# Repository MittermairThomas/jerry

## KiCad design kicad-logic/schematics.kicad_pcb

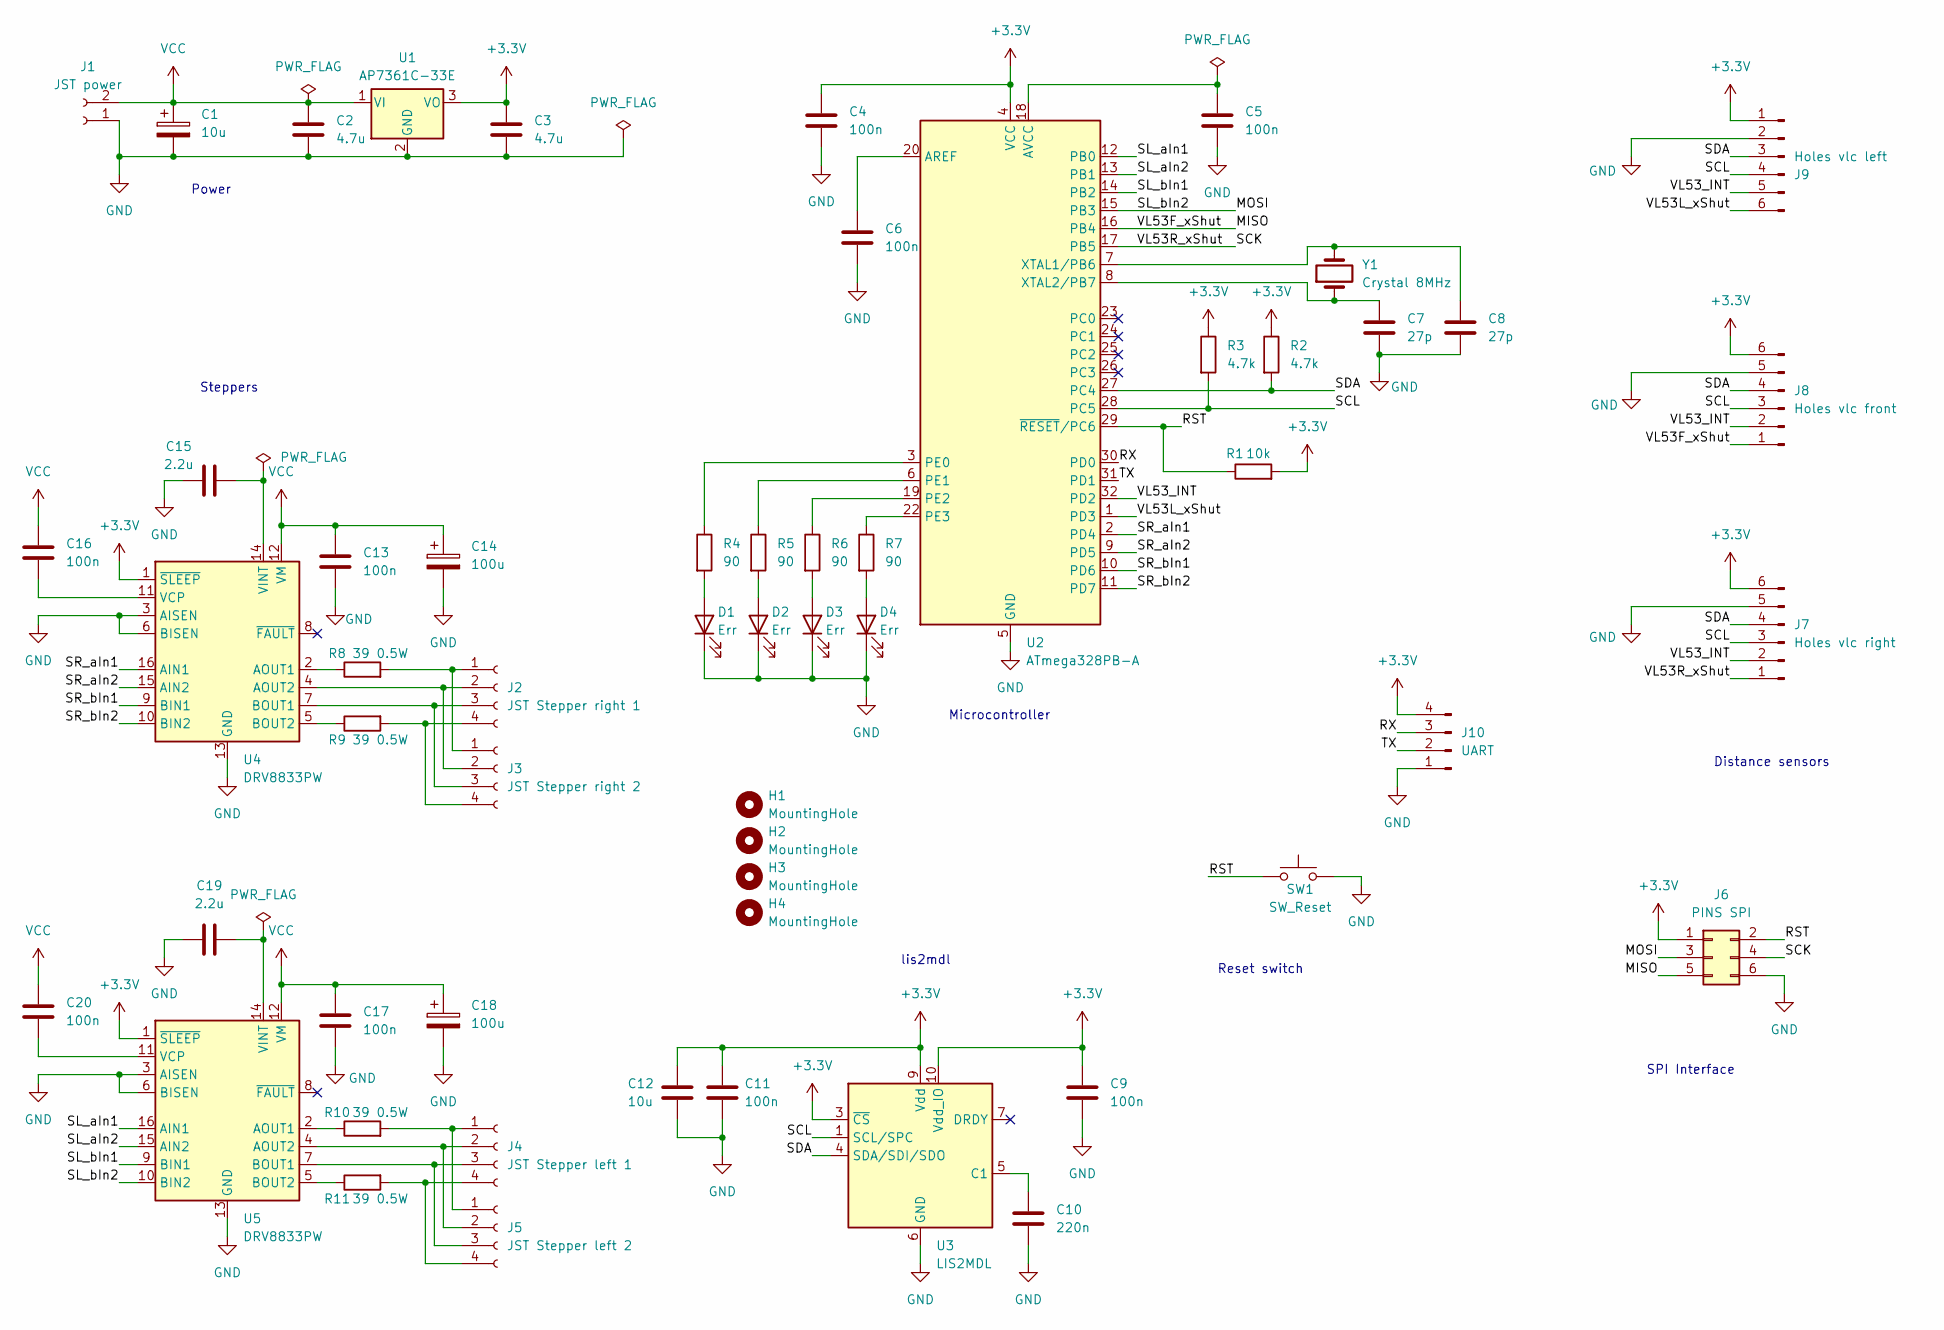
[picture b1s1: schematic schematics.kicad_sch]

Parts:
C1: 10u; CP_Radial_D6.3mm_P2.50mm
C2, C3: 4.7u; C_0603_1608Metric
C4, C5, C6, C9, C11, C13, C16, C17, C20: 100n; C_0603_1608Metric
C7, C8: 27p; C_0402_1005Metric
C10: 220n; C_0603_1608Metric
C12: 10u; C_1206_3216Metric
C14, C18: 100u; CP_Radial_D6.3mm_P2.50mm
C15, C19: 2.2u; C_0603_1608Metric
D1, D2, D3, D4: Err; LED_0603_1608Metric
H1, H2, H3, H4: MountingHole; MountingHole_2.2mm_M2_Pad_Via
J1: JST power; Molex_KK-254_AE-6410-02A_1x02_P2.54mm_Vertical
J2: JST Stepper right 1; Molex_KK-254_AE-6410-04A_1x04_P2.54mm_Vertical
J3: JST Stepper right 2; Molex_KK-254_AE-6410-04A_1x04_P2.54mm_Vertical
J4: JST Stepper left 1; Molex_KK-254_AE-6410-04A_1x04_P2.54mm_Vertical
J5: JST Stepper left 2; Molex_KK-254_AE-6410-04A_1x04_P2.54mm_Vertical
J6: PINS SPI; PinHeader_2x03_P2.54mm_Vertical
J7: Holes vlc right; PinHeader_1x06_P2.54mm_Vertical
J8: Holes vlc front; PinHeader_1x06_P2.54mm_Vertical
J9: Holes vlc left; PinHeader_1x06_P2.54mm_Vertical
J10: UART; PinHeader_1x04_P2.54mm_Vertical
R1: 10k; R_0805_2012Metric
R2, R3: 4.7k; R_0805_2012Metric
R4, R5, R6, R7: 90; R_0805_2012Metric
R8, R9, R10, R11: 39 0.5W; R_Axial_DIN0207_L6.3mm_D2.5mm_P10.16mm_Horizontal
SW1: SW_Reset; SW_PUSH_6mm
U1: AP7361C-33E; SOT-223-3_TabPin2
U2: ATmega328PB-A; TQFP-32_7x7mm_P0.8mm
U3: LIS2MDL; LGA-12_2x2mm_P0.5mm
U4, U5: DRV8833PW; TSSOP-16-1EP_4.4x5mm_P0.65mm
Y1: Crystal 8MHz; Crystal_SMD_3225-4Pin_3.2x2.5mm

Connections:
+3.3V: C3.1, C4.1, C9.1, C11.1, C12.1, J6.1, J7.6, J8.6, J9.1, J10.4, R1.2, R2.1, R3.1, U1.3 (VO), U2.4 (VCC), U3.3 (~CS), U3.9 (Vdd), U3.10 (Vdd_IO), U4.1 (~SLEEP), U5.1 (~SLEEP)
/MISO: J6.5, J8.1, U2.16 (PB4)
/MOSI: J6.3, U2.15 (PB3), U5.10 (BIN2)
/RST: J6.2, R1.1, SW1.1, U2.29 (~RESET/PC6)
/RX: J10.3, U2.30 (PD0)
/SCK: J6.4, J7.1, U2.17 (PB5)
/SCL: J7.3, J8.3, J9.4, R3.2, U2.28 (PC5), U3.1 (SCL/SPC)
/SDA: J7.4, J8.4, J9.3, R2.2, U2.27 (PC4), U3.4 (SDA/SDI/SDO)
/SL_aIn1: U2.12 (PB0), U5.16 (AIN1)
/SL_aIn2: U2.13 (PB1), U5.15 (AIN2)
/SL_bIn1: U2.14 (PB2), U5.9 (BIN1)
/SR_aIn1: U2.2 (PD4), U4.16 (AIN1)
/SR_aIn2: U2.9 (PD5), U4.15 (AIN2)
/SR_bIn1: U2.10 (PD6), U4.9 (BIN1)
/SR_bIn2: U2.11 (PD7), U4.10 (BIN2)
/TX: J10.2, U2.31 (PD1)
/VL53L_xShut: J9.6, U2.1 (PD3)
/VL53_INT: J7.2, J8.2, J9.5, U2.32 (PD2)
GND: C1.2, C2.2, C3.2, C4.2, C5.2, C6.2, C7.2, C8.2, C9.2, C10.1, C11.2, C12.2, C13.2, C14.2, C15.1, C17.2, C18.2, C19.1, D1.1 (K), D2.1 (K), D3.1 (K), D4.1 (K), J1.1, J6.6, J7.5, J8.5, J9.2, J10.1, SW1.2, U1.2 (GND), U2.5 (GND), U2.21 (GND), U3.6 (GND), U3.8 (GND), U4.3 (AISEN), U4.6 (BISEN), U4.13 (GND), U5.3 (AISEN), U5.6 (BISEN), U5.13 (GND)
unnamed: D1.2 (A), R4.2
unnamed: D2.2 (A), R5.2
unnamed: D3.2 (A), R6.2
unnamed: D4.2 (A), R7.2
unnamed: J2.1, J3.1, R8.2
unnamed: J2.2, J3.2, U4.4 (AOUT2)
unnamed: J2.3, J3.3, U4.7 (BOUT1)
unnamed: J2.4, J3.4, R9.2
unnamed: J4.1, J5.1, R10.2
unnamed: J4.2, J5.2, U5.4 (AOUT2)
unnamed: J4.3, J5.3, U5.7 (BOUT1)
unnamed: J4.4, J5.4, R11.2
unnamed: C6.1, U2.20 (AREF)
unnamed: C5.1, U2.18 (AVCC)
unnamed: R4.1, U2.3 (PE0)
unnamed: R5.1, U2.6 (PE1)
unnamed: R6.1, U2.19 (PE2)
unnamed: R7.1, U2.22 (PE3)
unnamed: C8.1, U2.7 (XTAL1/PB6), Y1.2
unnamed: C7.1, U2.8 (XTAL2/PB7), Y1.1
unnamed: C10.2, U3.5 (C1)
unnamed: R8.1, U4.2 (AOUT1)
unnamed: R9.1, U4.5 (BOUT2)
unnamed: C16.2, U4.11 (VCP)
unnamed: C15.2, U4.14 (VINT)
unnamed: R10.1, U5.2 (AOUT1)
unnamed: R11.1, U5.5 (BOUT2)
unnamed: C20.2, U5.11 (VCP)
unnamed: C19.2, U5.14 (VINT)
VCC: C1.1, C2.1, C13.1, C14.1, C16.1, C17.1, C18.1, C20.1, J1.2, U1.1 (VI), U4.12 (VM), U5.12 (VM)

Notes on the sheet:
SPI Interface
Distance sensors
Microcontroller
Power
Steppers
lis2mdl
Reset switch

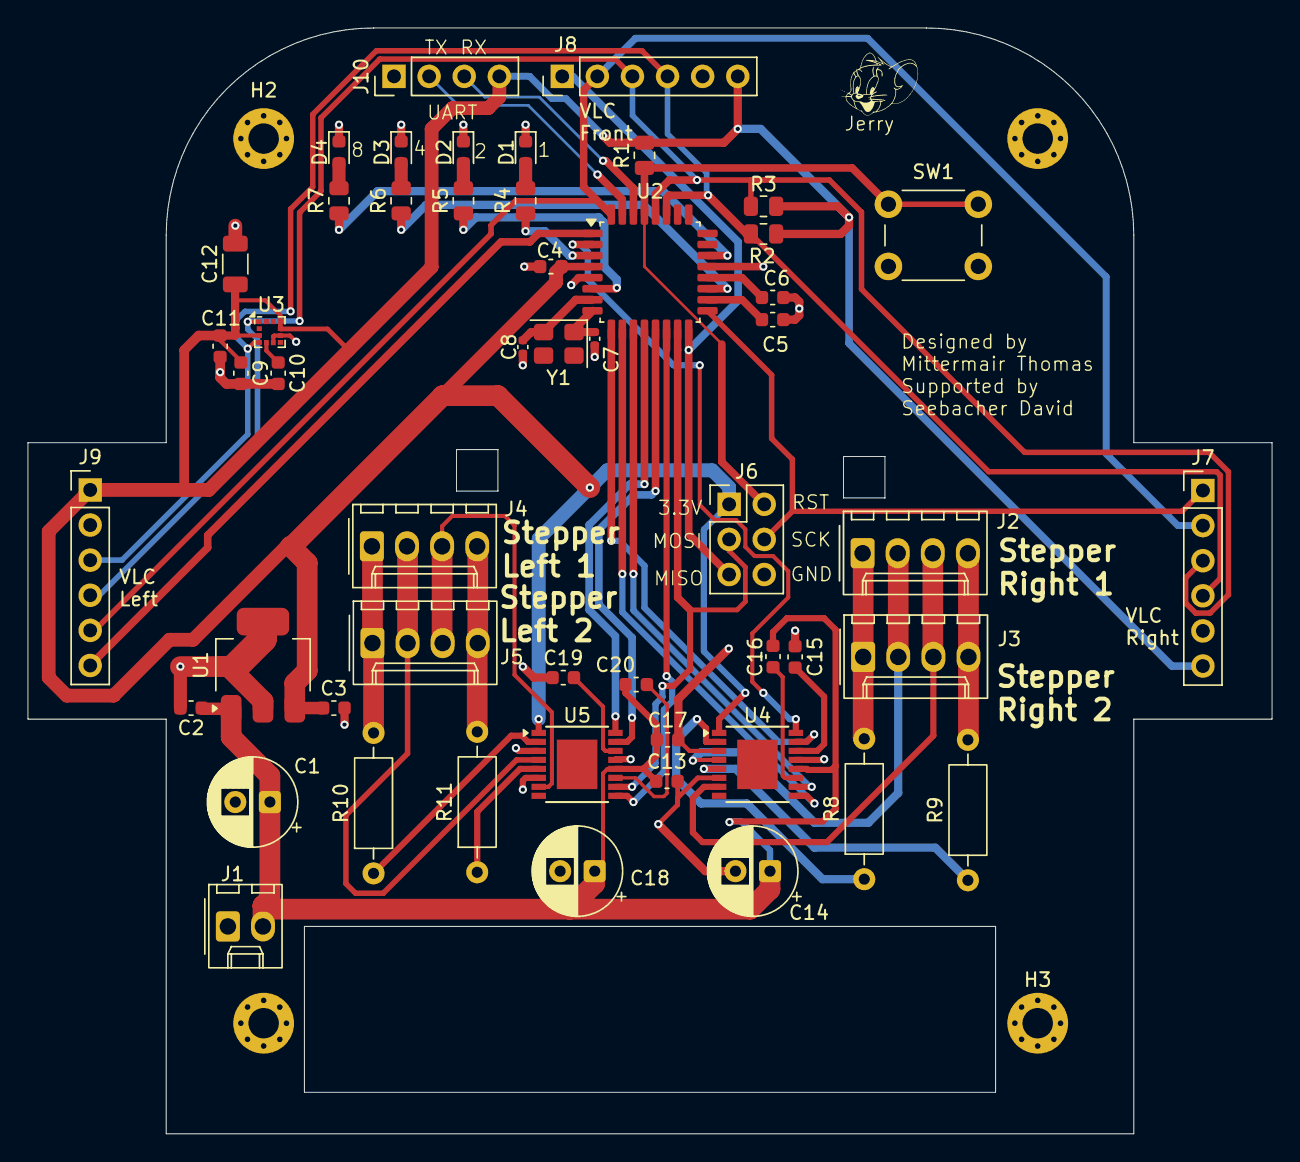
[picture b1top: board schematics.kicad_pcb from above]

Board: 2 copper layers, 90.0 x 80.0 mm, 56 parts (0 on the bottom side), 49 nets.
